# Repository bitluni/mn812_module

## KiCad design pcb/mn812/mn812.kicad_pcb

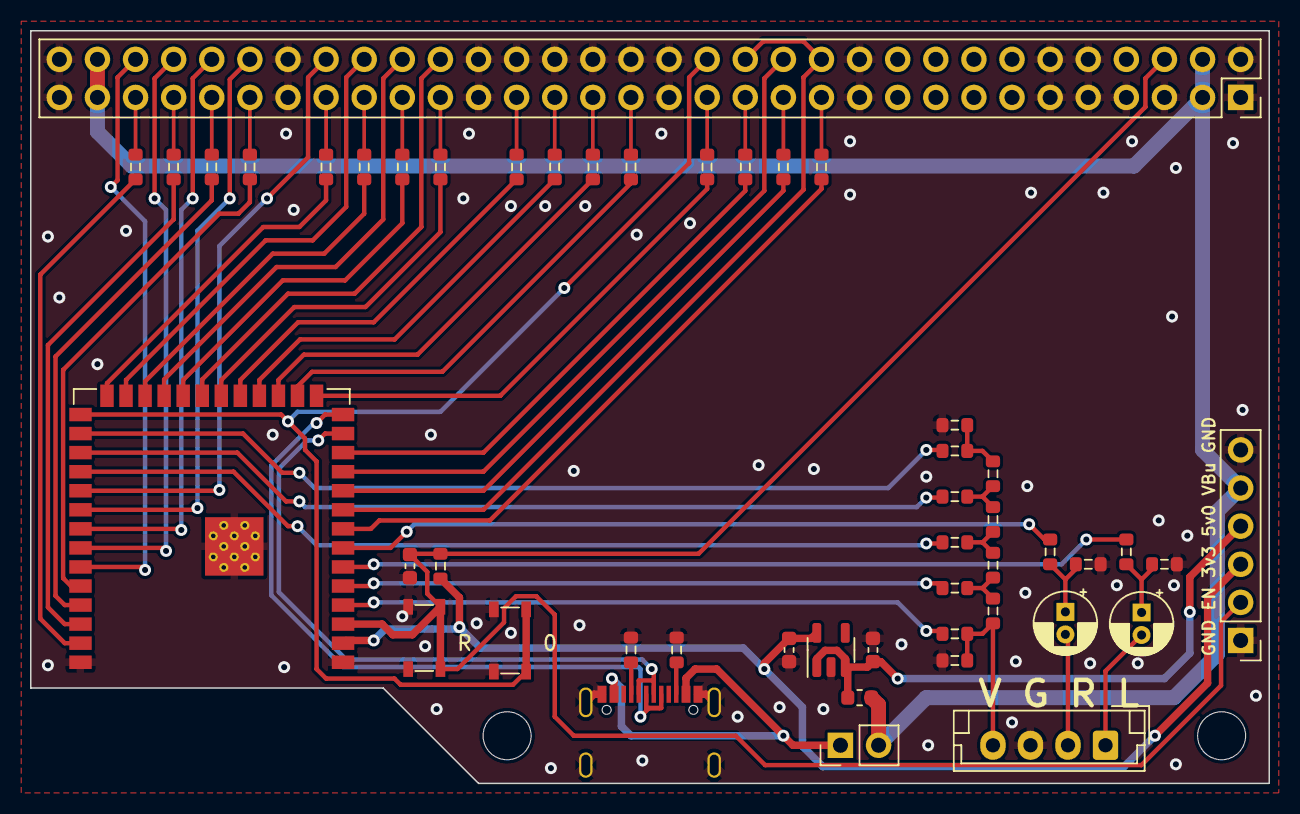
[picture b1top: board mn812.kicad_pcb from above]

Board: 2 copper layers, 82.6 x 50.2 mm, 51 parts (0 on the bottom side), 69 nets.

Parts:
C1: 10u; C_0603
C2, C3: 100n; C_0603
C4, C5: 100n; CP_Radial_D4.0mm_P1.50mm
F1: Polyfuse; Fuse_0603_1608Metric
H1, H2: MountingHole; MountingHole_3.2mm_M3
IC1: ESP32-S3-WROOM-1-N8R2; ESP32-S3-WROOM-1
J1: Conn_01x02_Pin; PinHeader_1x02_P2.54mm_Vertical
J2: Conn_01x04_Pin; JST_EH_B4B-EH-A_1x04_P2.50mm_Vertical
J3: Conn_02x32_Row_Letter_Last; PinSocket_2x32_P2.54mm_Vertical_ab
J4: Conn_01x06_Pin; PinHeader_1x06_P2.54mm_Vertical
PS1: TLV75733PDBVR; SOT-23-5
R1, R3, R5, R6, R7, R8, R9, R10, R11, R12, R13, R14, R15, R16, R18, R19: 1000; R_0603
R2, R17, R24, R29, R31, R36: 300; R_0603
R4, R20, R27, R34: 150; R_0603
R21, R22, R25, R26, R30: 82; R_0603
R23, R37: 5.1k; R_0603
R39: 10k; R_0603
SW1, SW2: miniButton; ButtonSMD3.2x2.5
U1: USB-C

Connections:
5V: C1.1, F1.2, J4.4, PS1.1 (IN), PS1.3 (EN)
+3V3: C2.1, IC1.2 (3V3), J4.3, PS1.5 (OUT), R39.2
A0: IC1.35 (IO42), J3.30a
A1: IC1.34 (IO41), J3.29a
A2: IC1.33 (IO40), J3.28a
A3: IC1.32 (IO39), J3.27a
A4: IC1.31 (IO38), J3.25a
A5: IC1.25 (IO48), J3.24a
A6: IC1.23 (IO21), J3.23a
A7: IC1.21 (IO13), J3.22a
CLK: IC1.27 (IO0), J3.15a, SW2.2
D0: J3.30b, R1.1
D1: J3.29b, R3.1
D2: J3.28b, R5.1
D3: J3.27b, R6.1
D4: J3.25b, R7.1
D5: J3.24b, R8.1
D6: J3.23b, R9.1
D7: J3.22b, R10.1
D8: J3.20b, R11.1
D9: J3.19b, R12.1
D10: J3.18b, R13.1
D11: J3.17b, R14.1
D12: J3.15b, R15.1
D13: J3.14b, R16.1
D14: J3.13b, R18.1
D15: J3.12b, R19.1
DN: IC1.13 (IO19), U1.5 (DN2), U1.7 (DN1)
DP: IC1.14 (IO20), U1.6 (DP1), U1.8 (DP2)
EN: C3.1, IC1.3 (EN), J3.3a, J4.2, R39.1, SW1.2
GND: C1.2, C2.2, C3.2, IC1.1 (GND_1), IC1.40 (GND_2), IC1.41 (GND_3), J2.3, J3.1a, J3.1b, J3.3b, J3.4b, J3.5a, J3.5b, J3.6a, J3.6b, J3.11a, J3.11b, J3.16a, J3.16b, J3.17a, J3.18a, J3.19a, J3.20a, J3.21a, J3.21b, J3.26a, J3.26b, J3.32a, J3.32b, J4.1, J4.6, PS1.2 (GND), R2.2, R21.2, R22.2, R23.1, R30.2, R37.2, SW1.1, SW2.1, U1.0 (Shield), U1.1 (GND), U1.12 (GND)
IO1: IC1.39 (IO1), R1.2
IO2: IC1.38 (IO2), R3.2
IO3: IC1.15 (IO3), R15.2
IO4: IC1.4 (IO4), R31.1
IO5: IC1.5 (IO5), R24.1
IO6: IC1.6 (IO6), R25.2
IO7: IC1.7 (IO7), R26.2
IO8: IC1.12 (IO8), R16.2
IO9: IC1.17 (IO9), R13.2
IO10: IC1.18 (IO10), R12.2
IO11: IC1.19 (IO11), R11.2
IO12: IC1.20 (IO12), R10.2
IO14: IC1.22 (IO14), R9.2
IO15: IC1.8 (IO15), R19.2
IO16: IC1.9 (IO16), J3.12a, J3.14a
IO17: IC1.10 (IO17), R18.2
IO18: IC1.11 (IO18), J3.13a
IO35: IC1.28 (IO35), R29.1
IO36: IC1.29 (IO36), R36.1
IO37: IC1.30 (IO37), R17.1
IO43: IC1.37 (TXD0), R5.2
IO44: IC1.36 (RXD0), R6.2
IO45: IC1.26 (IO45), R7.2
IO46: IC1.16 (IO46), R14.2
IO47: IC1.24 (IO47), R8.2
L: C4.2, J2.1
unnamed: C4.1, R21.1, R25.1
unnamed: C5.1, R22.1, R26.1
unnamed: R2.1, R29.2, R34.2
unnamed: R4.1, R17.2, R20.2
unnamed: R20.1, R24.2, R27.2
unnamed: R4.2, R34.1, R36.2
unnamed: R23.2, U1.4 (CC1)
unnamed: R37.1, U1.10 (CC2)
R: C5.2, J2.2
V: J2.4, R27.1, R30.1, R31.2
VBUS: J1.1, U1.2 (VBUS), U1.11 (VBUS)
VBUS2: F1.1, J1.2, J3.2a, J3.2b, J3.31a, J3.31b, J4.5

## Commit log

2023-12-06 working version before stream
2023-12-20 massstorage works
2023-12-20 fixed flash size
2023-12-21 loading files but bad
2023-12-21 spi ram support and fixed size bug. memory issues solved
2023-12-21 CDC added but no worky yet
2023-12-27 drum pad experiment
